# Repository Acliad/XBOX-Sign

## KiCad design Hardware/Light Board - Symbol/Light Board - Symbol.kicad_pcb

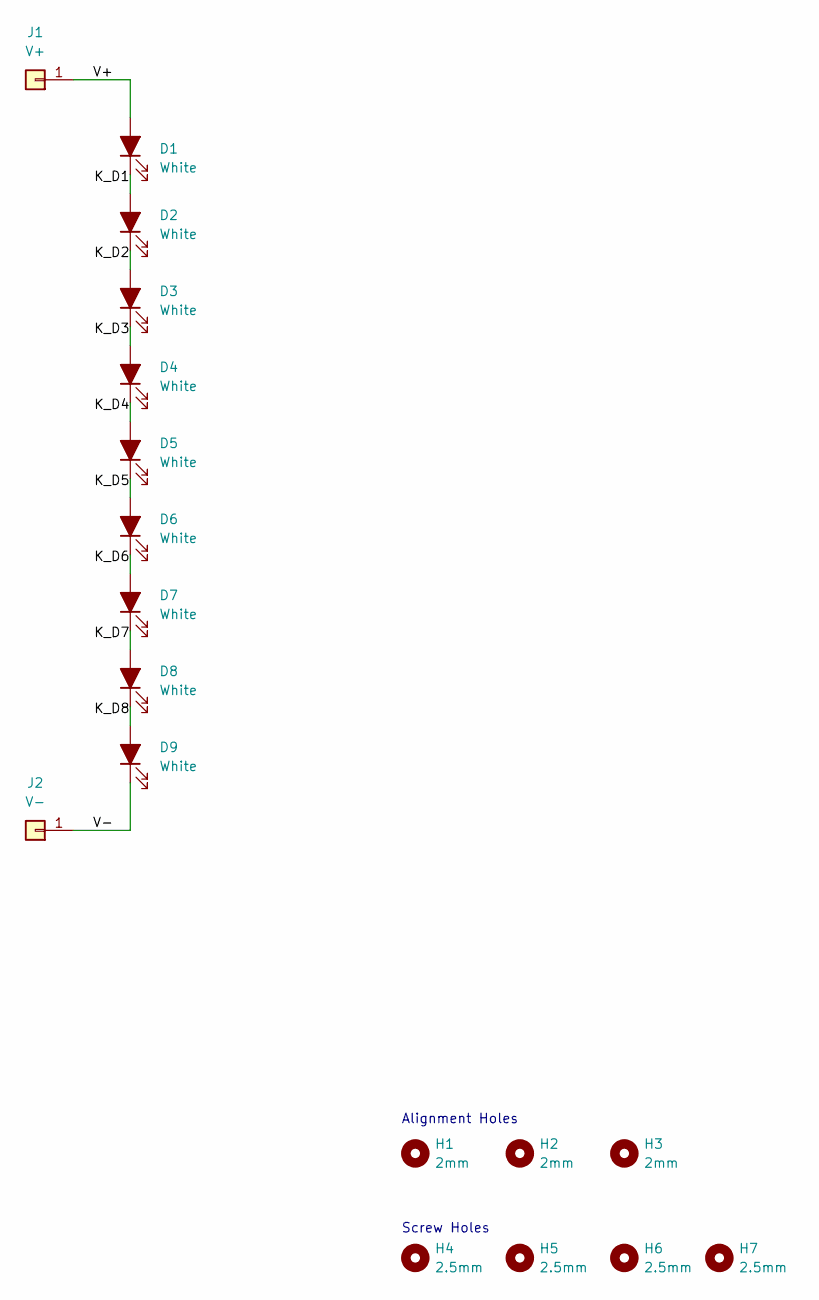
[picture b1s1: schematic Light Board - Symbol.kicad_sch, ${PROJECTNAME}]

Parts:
D1, D2, D3, D4, D5, D6, D7, D8, D9: White; LED_Cree_J-Series_SMD2835_2.8x3.5mm; MPN JB2835AWT-W-H40GA0000-N0000001; DigiKey PN 2138-JB2835AWT-W-H40GA0000-N0000001CT-ND
H1, H2, H3: 2mm; MountingHole_2.0mm_M2_ReducedCourtyard
H4, H5, H6, H7: 2.5mm; MountingHole_2.5mm
J1: V+; TestPoint_Pad_2.0x2.0mm
J2: V-; TestPoint_Pad_2.0x2.0mm

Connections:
/K_D1: D1.1 (K), D2.2 (A)
/K_D2: D2.1 (K), D3.2 (A)
/K_D3: D3.1 (K), D4.2 (A)
/K_D4: D4.1 (K), D5.2 (A)
/K_D5: D5.1 (K), D6.2 (A)
/K_D6: D6.1 (K), D7.2 (A)
/K_D7: D7.1 (K), D8.2 (A)
/K_D8: D8.1 (K), D9.2 (A)
/V+: D1.2 (A), J1.1
/V-: D9.1 (K), J2.1

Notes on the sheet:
Alignment Holes
Screw Holes

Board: 2 copper layers, 18 parts (0 on the bottom side), 10 nets, no tracks yet.

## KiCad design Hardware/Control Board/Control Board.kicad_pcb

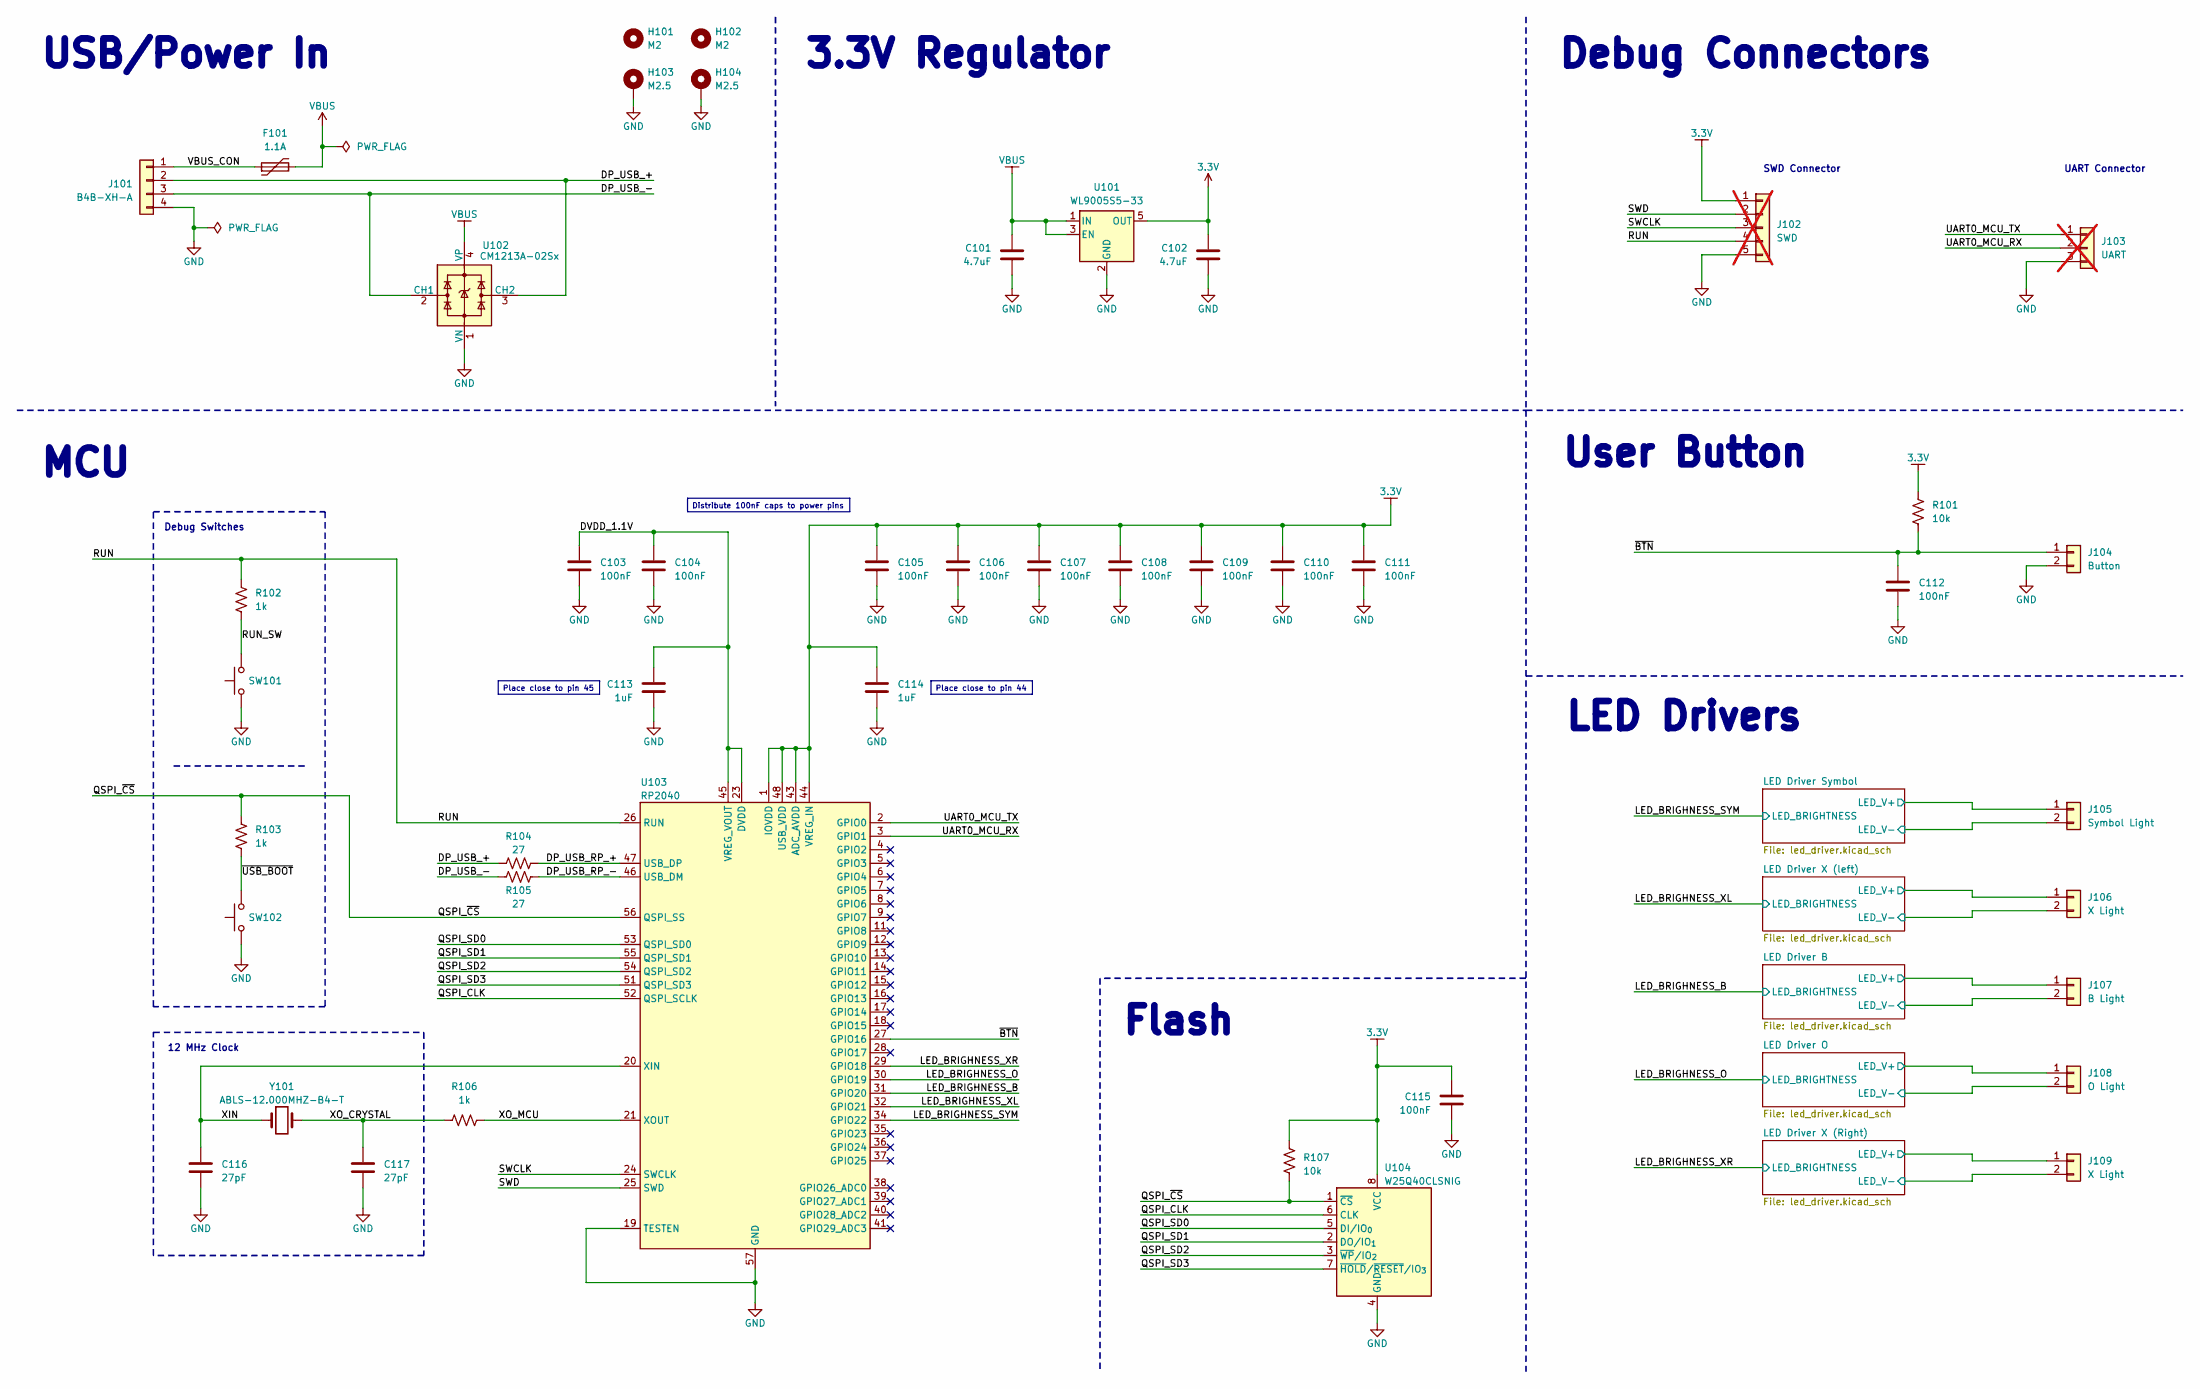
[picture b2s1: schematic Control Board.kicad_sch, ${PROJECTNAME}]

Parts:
C101, C102: 4.7uF; C_0603_1608Metric; MPN CL10A475KP8NNNC; LCSC PN C1705
C103, C104, C105, C106, C107, C108, C109, C110, C111, C112, C115: 100nF; C_0402_1005Metric; MPN CL05B104KO5NNNC; DigiKey PN 1276-1006-1-ND
C113, C114: 1uF; C_0402_1005Metric; MPN CL05A105KA5NQNC; DigiKey PN 1276-6524-1-ND
C116, C117: 27pF; C_0402_1005Metric; MPN CC0402FRNPO9BN270; DigiKey PN 1276-2247-1-ND
F101: 1.1A; Fuse_1206_3216Metric; MPN NANOSMDC050F/13.2-2; LCSC PN C2649911
H101, H102: M2; MountingHole_2.0mm_M2_ReducedCourtyard
H103, H104: M2.5; MountingHole_2.5mm_Pad
J101: B4B-XH-A; JST_XH_B4B-XH-A_1x04_P2.50mm_Vertical; MPN B4B-XH-A; DigiKey PN 455-2237-ND
J102: SWD; PinHeader_1x05_P2.54mm_Vertical; MPN PZ254V-11-05P; DigiKey PN 2057-PH1-05-UA-ND; not fitted
J103: UART; PinHeader_1x03_P2.54mm_Vertical; MPN PZ254V-11-03P; LCSC PN C2937625; not fitted
J104: Button; PinHeader_1x02_P2.54mm_Vertical
J105: Symbol Light; PinHeader_1x02_P2.54mm_Vertical
J106, J109: X Light; PinHeader_1x02_P2.54mm_Vertical
J107: B Light; PinHeader_1x02_P2.54mm_Vertical
J108: O Light; PinHeader_1x02_P2.54mm_Vertical
R101: 10k; R_0402_1005Metric; MPN RC0402FR-0710KL; DigiKey PN CR0603-FX-27R0ELFCT-ND
R102, R103, R106: 1k; R_0402_1005Metric; MPN RC0402FR-071KL; DigiKey PN RNCP0603FTD1K00CT-ND
R104, R105: 27; R_0402_1005Metric; MPN RC0402FR-0727RL; DigiKey PN CR0603-FX-27R0ELFCT-ND
R107: 10k; R_0402_1005Metric; MPN RC0402FR-0710KL; DigiKey PN RNCP0603FTD1K00CT-ND
SW101, SW102: PTS636 SL43 SMTR LFS; SW-PUSH-6x3.5mm_CK-PTS636SL43x_HandSolder; MPN PTS636 SL43 SMTR LFS; DigiKey PN CKN12309-1-ND
U101: WL9005S5-33; SOT-23-5; MPN WL9005S5-33; LCSC PN C2688249
U102: CM1213A−02Sx; SOT-143; MPN CM1213A-02SR; LCSC PN C19268160
U103: RP2040; QFN-56-1EP_7x7mm_P0.4mm_EP3.2x3.2mm; MPN RP2040; DigiKey PN 2648-SC0914(13)CT-ND
U104: W25Q40CLSNIG; SOIC-8_3.9x4.9mm_P1.27mm; MPN W25Q40CLSNIG; DigiKey PN W25Q40CLSNIG-ND
Y101: ABLS-12.000MHZ-B4-T; Crystal_SMD_HC49-SD; MPN ABLS-12.000MHZ-B4-T; DigiKey PN 535-10218-1-ND

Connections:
3.3V: C102.1, C105.1, C106.1, C107.1, C108.1, C109.1, C110.1, C111.1, C114.1, C115.1, J102.1, R101.2, R107.1, U101.5 (OUT), U103.1 (IOVDD), U103.10 (IOVDD), U103.22 (IOVDD), U103.33 (IOVDD), U103.42 (IOVDD), U103.43 (ADC_AVDD), U103.44 (VREG_IN), U103.48 (USB_VDD), U103.49 (IOVDD), U104.8 (VCC)
/DP_USB_+: J101.2, R104.1, U102.3 (CH2)
/DP_USB_-: J101.3, R105.1, U102.2 (CH1)
/DP_USB_RP_+: R104.2, U103.47 (USB_DP)
/DP_USB_RP_-: R105.2, U103.46 (USB_DM)
/DVDD_1.1V: C103.1, C104.1, C113.1, U103.23 (DVDD), U103.45 (VREG_VOUT), U103.50 (DVDD)
/LED Driver B/LED_V+: J107.1; also elsewhere on the board
/LED Driver B/LED_V-: J107.2; also elsewhere on the board
/LED Driver O/LED_V+: J108.1; also elsewhere on the board
/LED Driver O/LED_V-: J108.2; also elsewhere on the board
/LED Driver Symbol/LED_V+: J105.1; also elsewhere on the board
/LED Driver Symbol/LED_V-: J105.2; also elsewhere on the board
/LED Driver X (Right)/LED_V+: J109.1; also elsewhere on the board
/LED Driver X (Right)/LED_V-: J109.2; also elsewhere on the board
/LED Driver X (left)/LED_V+: J106.1; also elsewhere on the board
/LED Driver X (left)/LED_V-: J106.2; also elsewhere on the board
/LED_BRIGHNESS_B: U103.31 (GPIO20); also elsewhere on the board
/LED_BRIGHNESS_O: U103.30 (GPIO19); also elsewhere on the board
/LED_BRIGHNESS_SYM: U103.34 (GPIO22); also elsewhere on the board
/LED_BRIGHNESS_XL: U103.32 (GPIO21); also elsewhere on the board
/LED_BRIGHNESS_XR: U103.29 (GPIO18); also elsewhere on the board
/QSPI_CLK: U103.52 (QSPI_SCLK), U104.6 (CLK)
/QSPI_SD0: U103.53 (QSPI_SD0), U104.5 (DI/IO_{0})
/QSPI_SD1: U103.55 (QSPI_SD1), U104.2 (DO/IO_{1})
/QSPI_SD2: U103.54 (QSPI_SD2), U104.3 (~WP/IO_{2})
/QSPI_SD3: U103.51 (QSPI_SD3), U104.7 (~HOLD/~RESET/IO_{3})
/QSPI_~CS: R103.2, R107.2, U103.56 (QSPI_SS), U104.1 (~CS)
/RUN: J102.4, R102.2, U103.26 (RUN)
/RUN_SW: R102.1, SW101.2
/SWCLK: J102.3, U103.24 (SWCLK)
/SWD: J102.2, U103.25 (SWD)
/UART0_MCU_RX: J103.2, U103.3 (GPIO1)
/UART0_MCU_TX: J103.1, U103.2 (GPIO0)
/VBUS_CON: F101.1, J101.1
/XIN: C116.1, U103.20 (XIN), Y101.1
/XO_CRYSTAL: C117.1, R106.1, Y101.2
/XO_MCU: R106.2, U103.21 (XOUT)
/~BTN: C112.1, J104.1, R101.1, U103.27 (GPIO16)
/~USB_BOOT: R103.1, SW102.2
GND: C101.2, C102.2, C103.2, C104.2, C105.2, C106.2, C107.2, C108.2, C109.2, C110.2, C111.2, C112.2, C113.2, C114.2, C115.2, C116.2, C117.2, H103.1, H104.1, J101.4, J102.5, J103.3, J104.2, SW101.1, SW102.1, U101.2 (GND), U102.1 (VN), U103.19 (TESTEN), U103.57 (GND), U104.4 (GND); also elsewhere on the board
VBUS: C101.1, F101.2, U101.1 (IN), U101.3 (EN), U102.4 (VP); also elsewhere on the board

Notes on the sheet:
LED Drivers
3.3V Regulator
12 MHz Clock
Debug Switches
SWD Connector
Flash
UART Connector
MCU
USB/Power In
Debug Connectors
User Button
Place close to pin 45
Place close to pin 44
Distribute 100nF caps to power pins

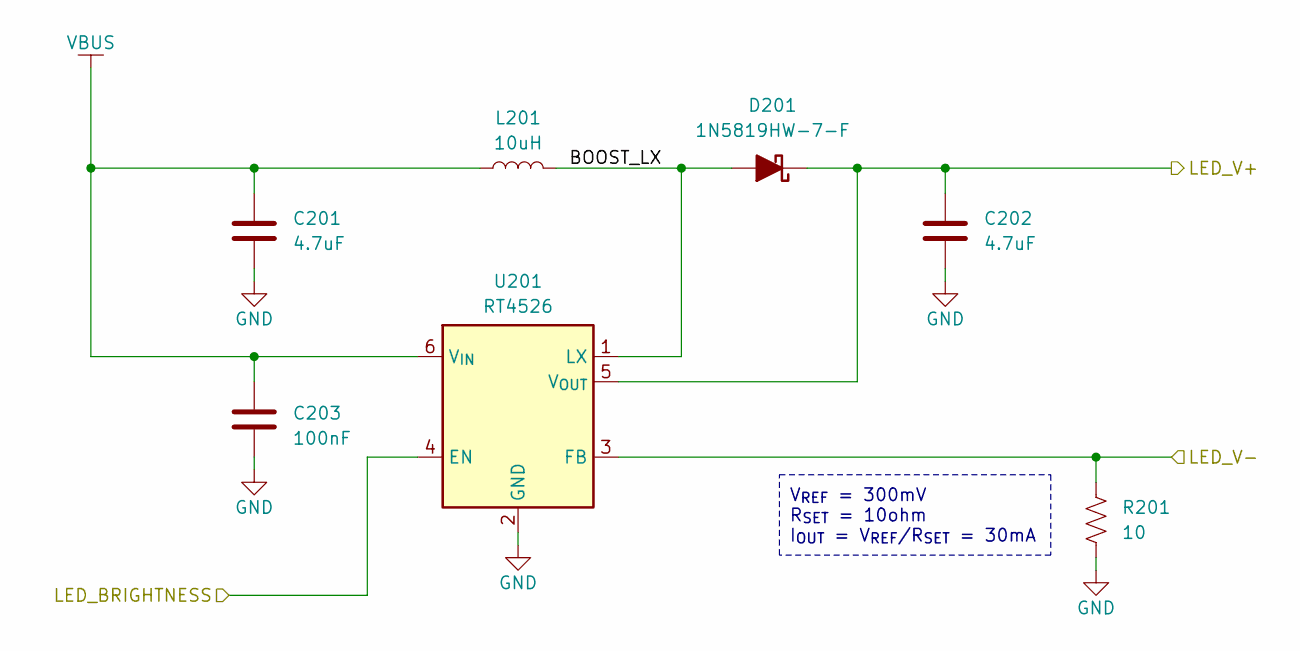
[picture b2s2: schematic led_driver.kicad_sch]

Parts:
C201: 4.7uF; C_0805_2012Metric; MPN CL21A475KBQNNNE; LCSC PN C98192
C202: 4.7uF; C_1206_3216Metric; MPN GRM31CR71H475KA12L; LCSC PN C77096
C203: 100nF; C_0402_1005Metric; MPN CL05B104KO5NNNC; DigiKey PN 1276-1006-1-ND
D201: 1N5819HW-7-F; D_SOD-123; MPN 1N5819HW-7-F; LCSC PN C82544
L201: 10uH; L_TDK_NLV25_2.5x2.0mm; MPN VLS252012HBX-100M-1; LCSC PN C88532
R201: 10; R_0402_1005Metric; MPN RC0402FR-0710RL; LCSC PN C138066
U201: RT4526; TSOT-23-6; MPN RT4526; LCSC PN C425168

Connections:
/LED Driver Symbol/BOOST_LX: D201.2 (A), L201.2, U201.1 (LX)
/LED Driver Symbol/LED_V+: C202.1, D201.1 (K), U201.5 (V_{OUT}); also elsewhere on the board
/LED Driver Symbol/LED_V-: R201.1, U201.3 (FB); also elsewhere on the board
/LED_BRIGHNESS_SYM: U201.4 (EN); also elsewhere on the board
GND: C201.2, C202.2, C203.2, R201.2, U201.2 (GND); also elsewhere on the board
VBUS: C201.1, C203.1, L201.1, U201.6 (V_{IN}); also elsewhere on the board

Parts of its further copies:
C301, C401, C501, C601: 4.7uF; C_0805_2012Metric; MPN CL21A475KBQNNNE; LCSC PN C98192
C302, C402, C502, C602: 4.7uF; C_1206_3216Metric; MPN GRM31CR71H475KA12L; LCSC PN C77096
C303, C403, C503, C603: 100nF; C_0402_1005Metric; MPN CL05B104KO5NNNC; DigiKey PN 1276-1006-1-ND
D301, D401, D501, D601: 1N5819HW-7-F; D_SOD-123; MPN 1N5819HW-7-F; LCSC PN C82544
L301, L401, L501, L601: 10uH; L_TDK_NLV25_2.5x2.0mm; MPN VLS252012HBX-100M-1; LCSC PN C88532
R301, R401, R501, R601: 10; R_0402_1005Metric; MPN RC0402FR-0710RL; LCSC PN C138066
U301, U401, U501, U601: RT4526; TSOT-23-6; MPN RT4526; LCSC PN C425168

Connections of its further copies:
/LED Driver B/BOOST_LX: D401.2 (A), L401.2, U401.1 (LX)
/LED Driver B/LED_V+: C402.1, D401.1 (K), U401.5 (V_{OUT}); also elsewhere on the board
/LED Driver B/LED_V-: R401.1, U401.3 (FB); also elsewhere on the board
/LED Driver O/BOOST_LX: D501.2 (A), L501.2, U501.1 (LX)
/LED Driver O/LED_V+: C502.1, D501.1 (K), U501.5 (V_{OUT}); also elsewhere on the board
/LED Driver O/LED_V-: R501.1, U501.3 (FB); also elsewhere on the board
/LED Driver X (Right)/BOOST_LX: D601.2 (A), L601.2, U601.1 (LX)
/LED Driver X (Right)/LED_V+: C602.1, D601.1 (K), U601.5 (V_{OUT}); also elsewhere on the board
/LED Driver X (Right)/LED_V-: R601.1, U601.3 (FB); also elsewhere on the board
/LED Driver X (left)/BOOST_LX: D301.2 (A), L301.2, U301.1 (LX)
/LED Driver X (left)/LED_V+: C302.1, D301.1 (K), U301.5 (V_{OUT}); also elsewhere on the board
/LED Driver X (left)/LED_V-: R301.1, U301.3 (FB); also elsewhere on the board
/LED_BRIGHNESS_B: U401.4 (EN); also elsewhere on the board
/LED_BRIGHNESS_O: U501.4 (EN); also elsewhere on the board
/LED_BRIGHNESS_XL: U301.4 (EN); also elsewhere on the board
/LED_BRIGHNESS_XR: U601.4 (EN); also elsewhere on the board
GND: C301.2, C302.2, C303.2, C401.2, C402.2, C403.2, C501.2, C502.2, C503.2, C601.2, C602.2, C603.2, R301.2, R401.2, R501.2, R601.2, U301.2 (GND), U401.2 (GND), U501.2 (GND), U601.2 (GND); also elsewhere on the board
VBUS: C301.1, C303.1, C401.1, C403.1, C501.1, C503.1, C601.1, C603.1, L301.1, L401.1, L501.1, L601.1, U301.6 (V_{IN}), U401.6 (V_{IN}), U501.6 (V_{IN}), U601.6 (V_{IN}); also elsewhere on the board

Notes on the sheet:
V_{REF} = 300mV R_{SET} = 10ohm I_{OUT} = V_{REF}/R_{SET} = 30mA

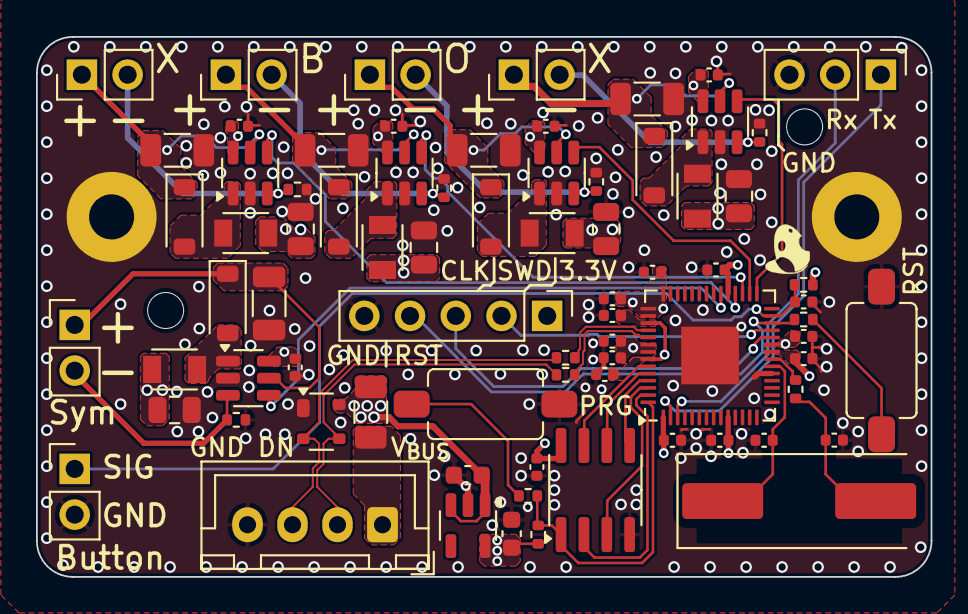
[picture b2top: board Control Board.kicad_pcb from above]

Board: 4 copper layers, 49.7 x 30.0 mm, 80 parts (0 on the bottom side), 46 nets.

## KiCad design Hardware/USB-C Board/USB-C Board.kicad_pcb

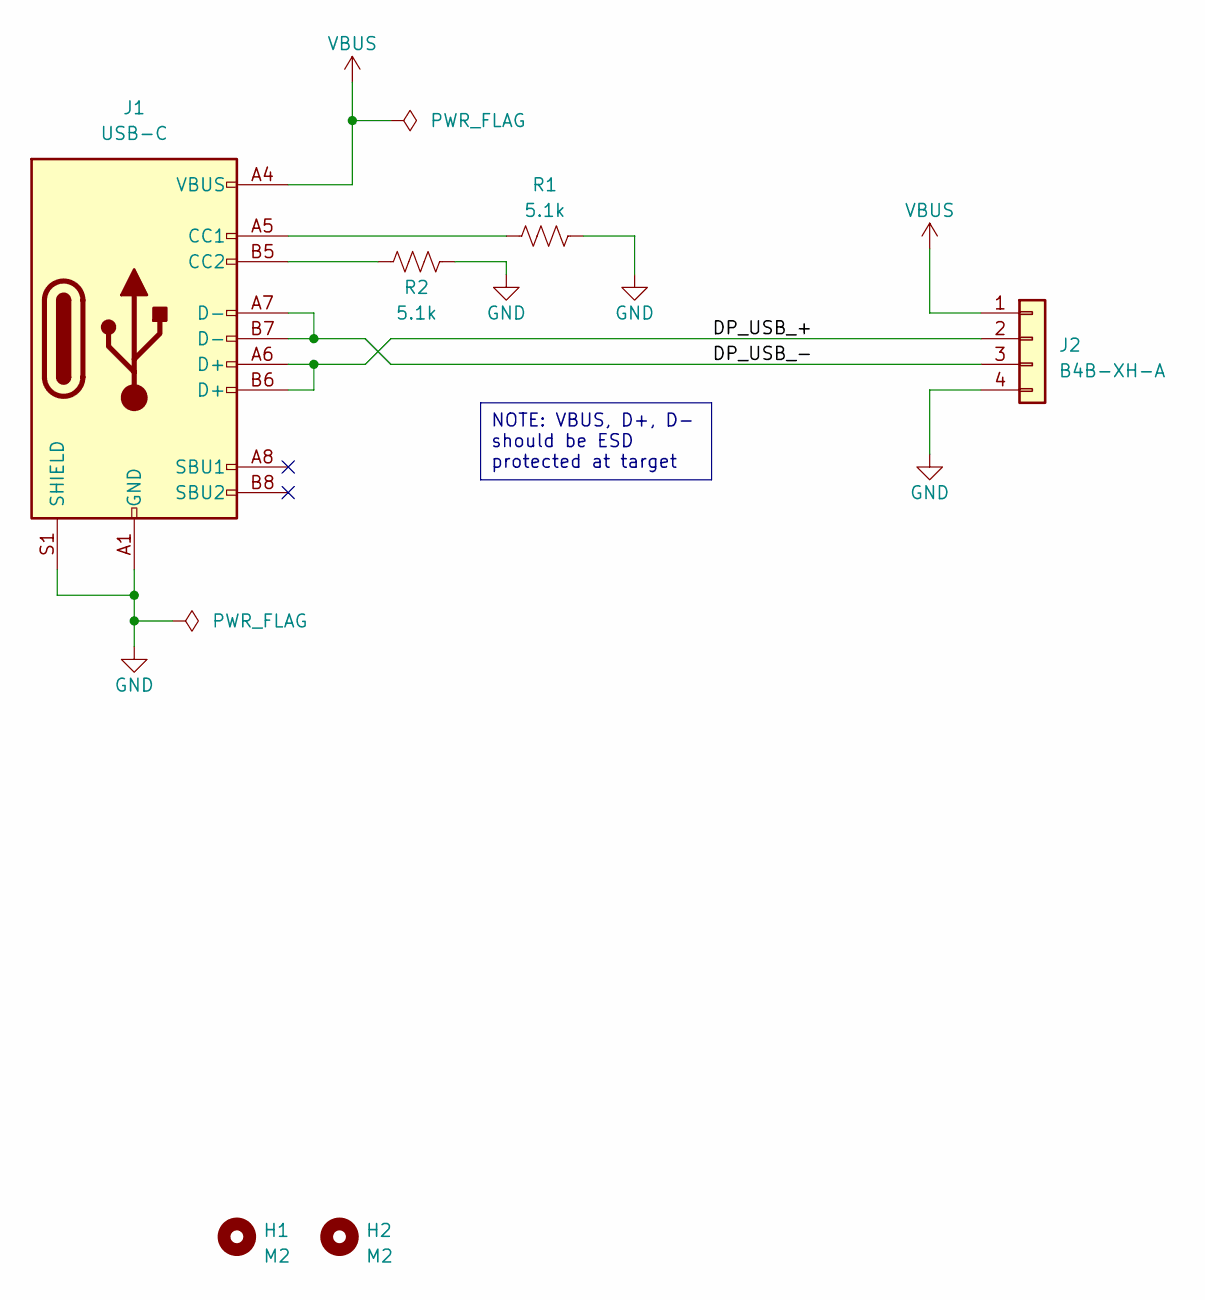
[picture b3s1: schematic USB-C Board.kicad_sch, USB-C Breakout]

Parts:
H1, H2: M2; MountingHole_2.2mm_M2
J1: USB-C; USB_C_Receptacle_GCT_USB4105-GF-A-060; MPN USB4105-GF-A-060; DigiKey PN 2073-USB4105-GF-A-060CT-ND
J2: B4B-XH-A; JST_XH_B4B-XH-A_1x04_P2.50mm_Vertical; MPN B4B-XH-A; DigiKey PN 455-2237-ND
R1, R2: 5.1k; R_0603_1608Metric; MPN VENDOR SELECT; DigiKey PN CR0603-FX-5101ELFCT-ND

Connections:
/DP_USB_+: J1.A6 (D+), J1.B6 (D+), J2.2
/DP_USB_-: J1.A7 (D-), J1.B7 (D-), J2.3
GND: J1.A1 (GND), J1.A12 (GND), J1.B1 (GND), J1.B12 (GND), J1.S1 (SHIELD), J2.4, R1.2, R2.2
unnamed: J1.A5 (CC1), R1.1
unnamed: J1.B5 (CC2), R2.1
VBUS: J1.A4 (VBUS), J1.A9 (VBUS), J1.B4 (VBUS), J1.B9 (VBUS), J2.1

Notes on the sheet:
NOTE: VBUS, D+, D- should be ESD protected at target

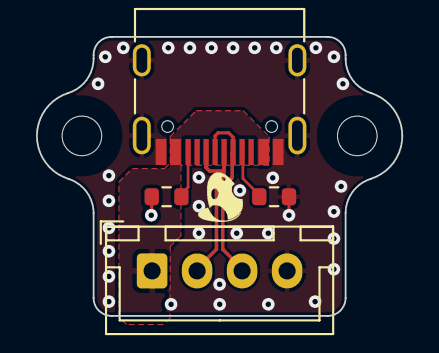
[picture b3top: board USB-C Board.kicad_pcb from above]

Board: 2 copper layers, 20.3 x 15.5 mm, 6 parts (0 on the bottom side), 6 nets.

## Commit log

2025-08-10 Iniital commit
2025-08-11 Added production file generation tools
2025-08-11 Added O lightboard
2025-08-16 Finished all light boards
2025-08-16 Added USB-C board
2025-08-16 Added control board
2025-08-16 Added stiching vias, 3D models
2025-08-16 Added release files
2025-08-16 Updated letter gerbers to 1 layer output
2025-08-25 Added note about incorrect footprint orientation
2025-08-30 Added LED library and fixed orientation
2025-09-19 Mid bringup, moving transistion from led.h to dedicated animation module
2025-09-21 Added base animation and transistion animation
2025-09-27 Added sweep animation
2025-09-28 Add button library
2025-09-28 Animations [essentially] finished
2025-09-28 Added state save and reprogram ability
2025-09-28 Add documentation to functions
